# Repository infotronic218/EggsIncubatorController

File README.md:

# Temperature and humidty controller
This project is designed for humidity and temperature regalation for eggs incubation. The project used a
Atmega328P, an NTC temperature sensor and a WHTM-02 Humidity and temperature sensor. The code is 
written in C programming language under AVR Studio Software.

# 3D View of the board

# PCB Layout View

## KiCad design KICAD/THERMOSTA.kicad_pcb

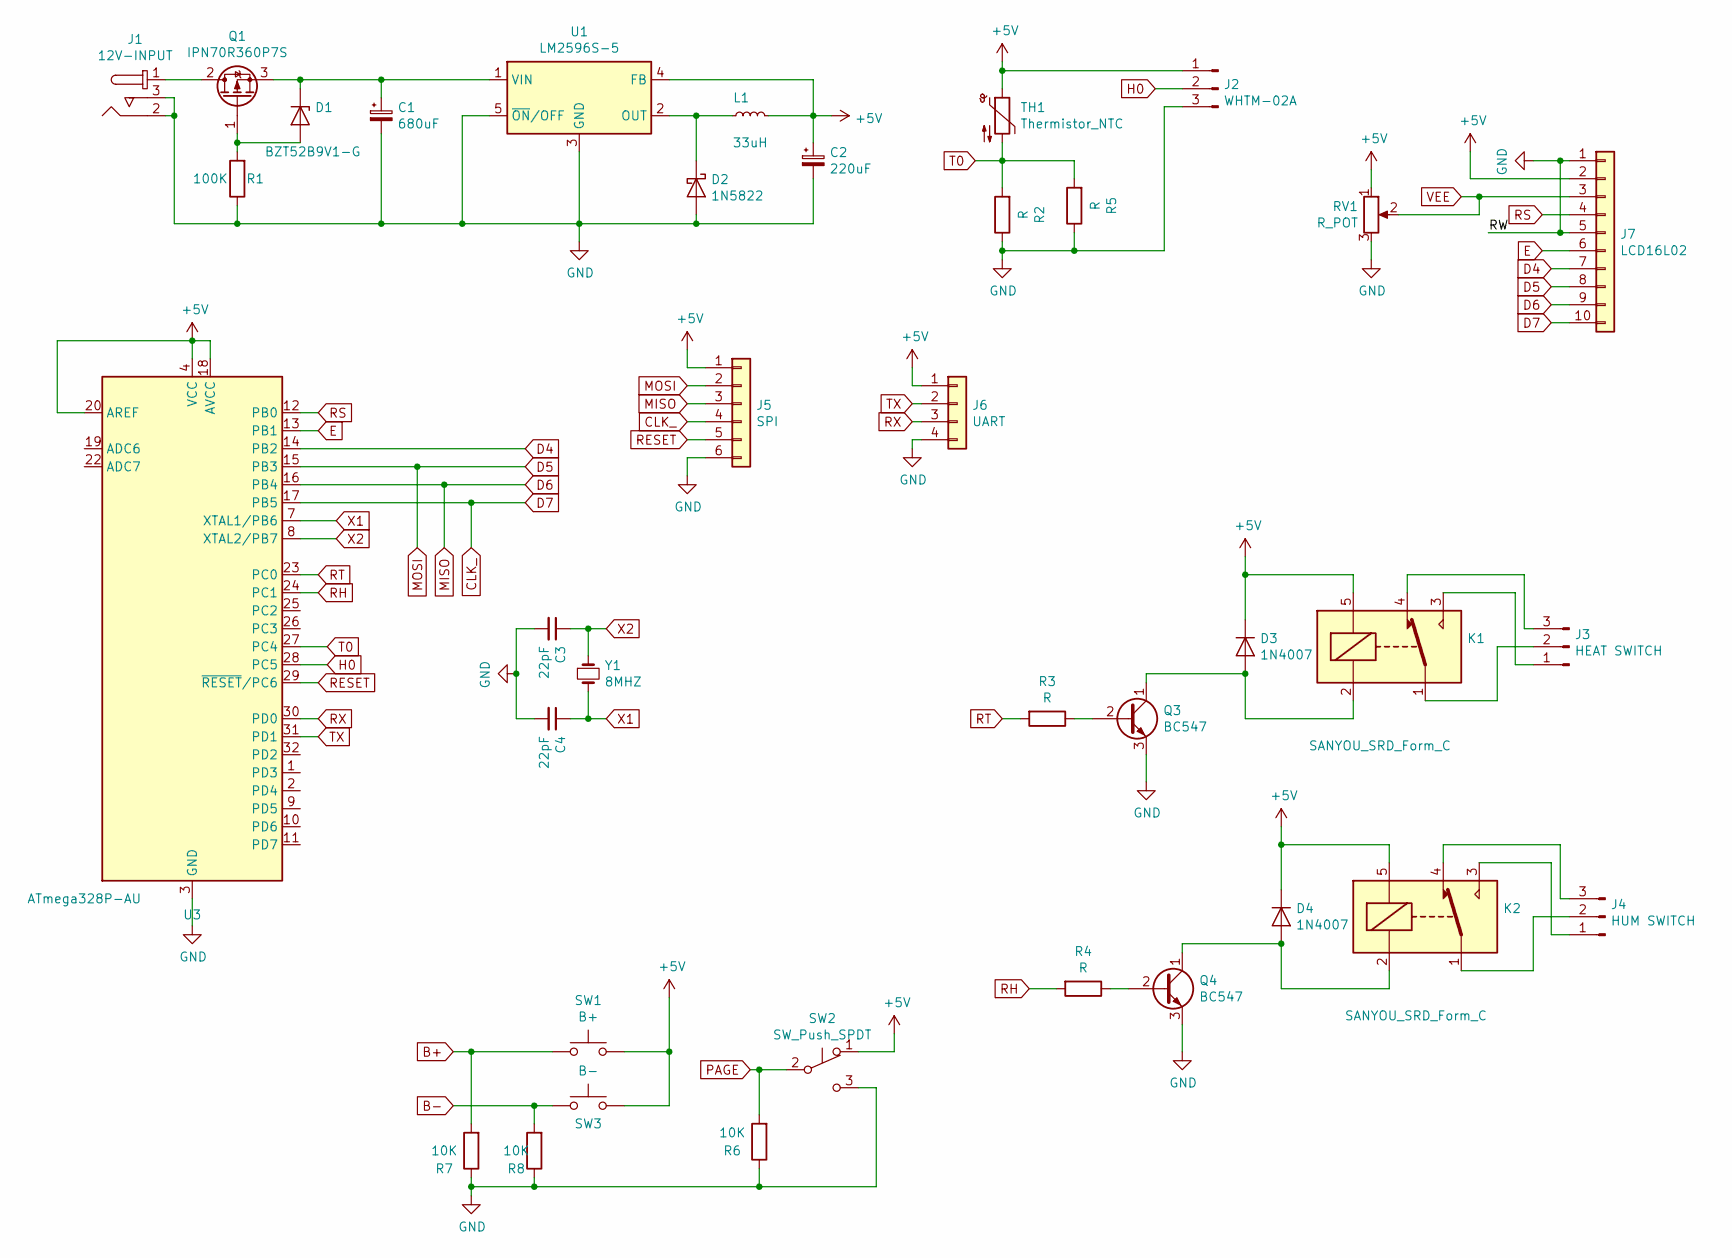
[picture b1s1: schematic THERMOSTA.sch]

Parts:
C1: 680uF; CP_Elec_5x5.3
C2: 220uF; CP_Elec_5x5.3
C3, C4: 22pF; C_0603_1608Metric
D1: BZT52B9V1-G; D_SOD-123
D2: 1N5822; D_SOD-123
D3, D4: 1N4007; D_DO-41_SOD81_P10.16mm_Horizontal
J1: 12V-INPUT; Barrel_Jack_5.5mmODx2.1mmID_PJ-102A; MPN PJ-102A; Digi-Key_PN CP-102A-ND
J2: WHTM-02A; JST_EH_B3B-EH-A_1x03_P2.50mm_Vertical
J3: HEAT SWITCH; TerminalBlock_MetzConnect_Type055_RT01503HDWU_1x03_P5.00mm_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
J4: HUM SWITCH; TerminalBlock_MetzConnect_Type055_RT01503HDWU_1x03_P5.00mm_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
J5: SPI; PinHeader_1x06_P2.54mm_Vertical
J6: UART; PinHeader_1x04_P2.54mm_Vertical
J7: LCD16L02; PinHeader_1x10_P2.54mm_Vertical
K1, K2: SANYOU_SRD_Form_C; Relay_SPDT_SANYOU_SRD_Series_Form_C
L1: 33uH; L_6.3x6.3_H3
Q1: IPN70R360P7S; SOT-223
Q3, Q4: BC547; SOT-23
R1: 100K; R_0805_2012Metric
R2: R; R_0805_2012Metric
R3, R4: R; R_1206_3216Metric
R5: R; R_Axial_DIN0207_L6.3mm_D2.5mm_P10.16mm_Horizontal
R6, R7, R8: 10K; R_1206_3216Metric
RV1: R_POT; Potentiometer_Bourns_3266W_Vertical
SW1: B+; SW_PUSH_6mm_H8mm
SW2: SW_Push_SPDT; PinSocket_1x03_P2.54mm_Vertical
SW3: B-; SW_PUSH_6mm_H8mm
TH1: Thermistor_NTC; JST_EH_B2B-EH-A_1x02_P2.50mm_Vertical
U1: LM2596S-5; TO-263-5_TabPin3
U3: ATmega328P-AU; TQFP-32_7x7mm_P0.8mm
Y1: 8MHZ; Crystal_HC49-4H_Vertical

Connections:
+5V: C2.1, D3.1 (K), D4.1 (K), J2.1, J5.1, J6.1, J7.2, K1.5, K2.5, L1.2, RV1.1, SW1.2, SW2.1 (A), SW3.2, TH1.1, U1.4 (FB), U3.4 (VCC), U3.6 (VCC), U3.18 (AVCC), U3.20 (AREF)
B+: R7.2, SW1.1
B-: R8.2, SW3.1
CLK_: J5.4, J7.10, U3.17 (PB5)
D4: J7.7, U3.14 (PB2)
D5: J5.2, J7.8, U3.15 (PB3)
D6: J5.3, J7.9, U3.16 (PB4)
E: J7.6, U3.13 (PB1)
GND: C1.2, C2.2, C3.2, C4.2, D2.2 (A), J1.2, J1.3, J2.3, J5.6, J6.4, J7.1, J7.5, Q3.3 (E), Q4.3 (E), R1.1, R2.1, R5.1, R6.1, R7.1, R8.1, RV1.3, SW2.3 (C), U1.3 (GND), U1.5 (~ON~/OFF), U3.3 (GND), U3.5 (GND), U3.21 (GND)
H0: J2.2, U3.28 (PC5)
unnamed: C1.1, D1.1 (K), Q1.3 (S), U1.1 (VIN)
unnamed: D1.2 (A), Q1.1 (G), R1.2
unnamed: D2.1 (K), L1.1, U1.2 (OUT)
unnamed: D3.2 (A), K1.2, Q3.1 (C)
unnamed: D4.2 (A), K2.2, Q4.1 (C)
unnamed: J1.1, Q1.2 (D)
unnamed: J3.1, K1.3
unnamed: J3.2, K1.1
unnamed: J3.3, K1.4
unnamed: J4.1, K2.3
unnamed: J4.2, K2.1
unnamed: J4.3, K2.4
unnamed: Q3.2 (B), R3.1
unnamed: Q4.2 (B), R4.1
PAGE: R6.2, SW2.2 (B)
RESET: J5.5, U3.29 (~RESET~/PC6)
RH: R4.2, U3.24 (PC1)
RS: J7.4, U3.12 (PB0)
RT: R3.2, U3.23 (PC0)
RX: J6.3, U3.30 (PD0)
T0: R2.2, R5.2, TH1.2, U3.27 (PC4)
TX: J6.2, U3.31 (PD1)
VEE: J7.3, RV1.2
X1: C4.1, U3.7 (XTAL1/PB6), Y1.2
X2: C3.1, U3.8 (XTAL2/PB7), Y1.1

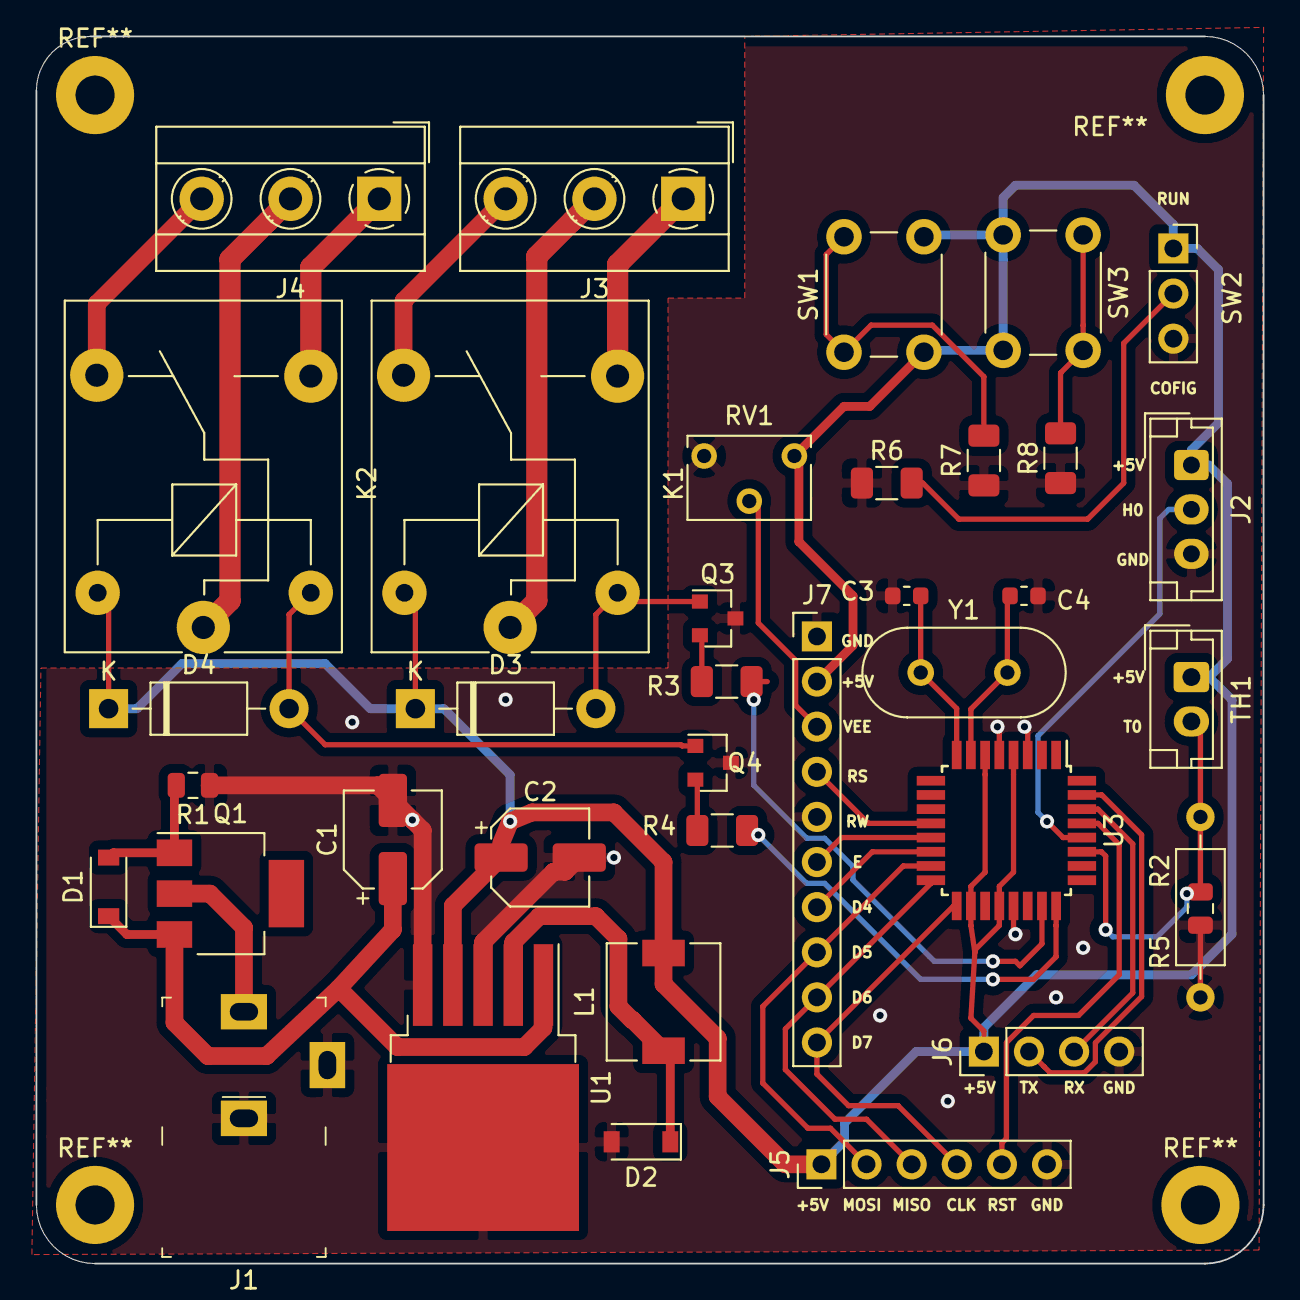
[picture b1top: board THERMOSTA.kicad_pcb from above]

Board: 2 copper layers, 69.1 x 69.1 mm, 37 parts (0 on the bottom side), 35 nets.

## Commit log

2021-01-04 update the images view
2021-01-22 Create test
